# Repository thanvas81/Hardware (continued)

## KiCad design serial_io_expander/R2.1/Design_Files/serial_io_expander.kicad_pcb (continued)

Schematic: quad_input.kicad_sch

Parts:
D8, D13, D18, D23: TBAW56,LM; SOT-23
RN9: 120K; R_Array_Concave_4x0603
RN10: 47K; R_Array_Concave_4x0603
U5, U6: PUMH11,115; SOT-363_SC-70-6

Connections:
/digital_inputs/COLLECTOR1: U6.3; also elsewhere on the board
/digital_inputs/COLLECTOR2: U6.6; also elsewhere on the board
/digital_inputs/COLLECTOR3: U5.6; also elsewhere on the board
/digital_inputs/COLLECTOR4: U5.3; also elsewhere on the board
/digital_inputs/IN1: RN9.8 (R1.2), RN10.5 (R4.2); also elsewhere on the board
/digital_inputs/IN2: RN9.7 (R2.2), RN10.6 (R3.2); also elsewhere on the board
/digital_inputs/IN3: RN9.6 (R3.2), RN10.7 (R2.2); also elsewhere on the board
/digital_inputs/IN4: RN9.5 (R4.2), RN10.8 (R1.2); also elsewhere on the board
/digital_inputs/quad_input1/+PULLUP: D8.3 (A), D13.3 (A); also elsewhere on the board
GND: D18.3 (A), D23.3 (A), U5.1, U5.4, U6.1, U6.4; also elsewhere on the board
unnamed: D23.1 (K), RN9.1 (R1.1), U5.5
unnamed: D23.2 (K), RN9.2 (R2.1), U5.2
unnamed: D18.2 (K), RN9.3 (R3.1), U6.2
unnamed: D18.1 (K), RN9.4 (R4.1), U6.5
unnamed: D13.2 (K), RN10.1 (R1.1)
unnamed: D13.1 (K), RN10.2 (R2.1)
unnamed: D8.2 (K), RN10.3 (R3.1)
unnamed: D8.1 (K), RN10.4 (R4.1)

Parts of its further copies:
D3, D4, D6, D7, D9, D10, D11, D12, D14, D15, D16, D17, D19, D20, D21, D22: TBAW56,LM; SOT-23
RN11, RN13, RN15, RN17: 47K; R_Array_Concave_4x0603
RN12, RN14, RN16, RN18: 120K; R_Array_Concave_4x0603
U15, U16, U21, U22, U27, U28, U33, U34: PUMH11,115; SOT-363_SC-70-6

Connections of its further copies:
/digital_inputs/COLLECTOR5: U16.3; also elsewhere on the board
/digital_inputs/COLLECTOR6: U16.6; also elsewhere on the board
/digital_inputs/COLLECTOR7: U15.6; also elsewhere on the board
/digital_inputs/COLLECTOR8: U15.3; also elsewhere on the board
/digital_inputs/COLLECTOR9: U22.3; also elsewhere on the board
/digital_inputs/COLLECTOR10: U22.6; also elsewhere on the board
/digital_inputs/COLLECTOR11: U21.6; also elsewhere on the board
/digital_inputs/COLLECTOR12: U21.3; also elsewhere on the board
/digital_inputs/COLLECTOR13: U34.3; also elsewhere on the board
/digital_inputs/COLLECTOR14: U34.6; also elsewhere on the board
/digital_inputs/COLLECTOR15: U33.6; also elsewhere on the board
/digital_inputs/COLLECTOR16: U33.3; also elsewhere on the board
/digital_inputs/COLLECTOR17: U28.3; also elsewhere on the board
/digital_inputs/COLLECTOR18: U28.6; also elsewhere on the board
/digital_inputs/COLLECTOR19: U27.6; also elsewhere on the board
/digital_inputs/COLLECTOR20: U27.3; also elsewhere on the board
/digital_inputs/IN5: RN11.5 (R4.2), RN12.8 (R1.2); also elsewhere on the board
/digital_inputs/IN6: RN11.6 (R3.2), RN12.7 (R2.2); also elsewhere on the board
/digital_inputs/IN7: RN11.7 (R2.2), RN12.6 (R3.2); also elsewhere on the board
/digital_inputs/IN8: RN11.8 (R1.2), RN12.5 (R4.2); also elsewhere on the board
/digital_inputs/IN9: RN13.5 (R4.2), RN14.8 (R1.2); also elsewhere on the board
/digital_inputs/IN10: RN13.6 (R3.2), RN14.7 (R2.2); also elsewhere on the board
/digital_inputs/IN11: RN13.7 (R2.2), RN14.6 (R3.2); also elsewhere on the board
/digital_inputs/IN12: RN13.8 (R1.2), RN14.5 (R4.2); also elsewhere on the board
/digital_inputs/IN13: RN17.5 (R4.2), RN18.8 (R1.2); also elsewhere on the board
/digital_inputs/IN14: RN17.6 (R3.2), RN18.7 (R2.2); also elsewhere on the board
/digital_inputs/IN15: RN17.7 (R2.2), RN18.6 (R3.2); also elsewhere on the board
/digital_inputs/IN16: RN17.8 (R1.2), RN18.5 (R4.2); also elsewhere on the board
/digital_inputs/IN17: RN15.5 (R4.2), RN16.8 (R1.2); also elsewhere on the board
/digital_inputs/IN18: RN15.6 (R3.2), RN16.7 (R2.2); also elsewhere on the board
/digital_inputs/IN19: RN15.7 (R2.2), RN16.6 (R3.2); also elsewhere on the board
/digital_inputs/IN20: RN15.8 (R1.2), RN16.5 (R4.2); also elsewhere on the board
/digital_inputs/quad_input1/+PULLUP: D3.3 (A), D4.3 (A), D6.3 (A), D7.3 (A), D9.3 (A), D10.3 (A), D11.3 (A), D12.3 (A); also elsewhere on the board
GND: D14.3 (A), D15.3 (A), D16.3 (A), D17.3 (A), D19.3 (A), D20.3 (A), D21.3 (A), D22.3 (A), U15.1, U15.4, U16.1, U16.4, U21.1, U21.4, U22.1, U22.4, U27.1, U27.4, U28.1, U28.4, U33.1, U33.4, U34.1, U34.4; also elsewhere on the board
unnamed: D9.2 (K), RN11.1 (R1.1)
unnamed: D9.1 (K), RN11.2 (R2.1)
unnamed: D3.2 (K), RN11.3 (R3.1)
unnamed: D3.1 (K), RN11.4 (R4.1)
unnamed: D19.1 (K), RN12.1 (R1.1), U15.5
unnamed: D19.2 (K), RN12.2 (R2.1), U15.2
unnamed: D14.2 (K), RN12.3 (R3.1), U16.2
unnamed: D14.1 (K), RN12.4 (R4.1), U16.5
unnamed: D10.2 (K), RN13.1 (R1.1)
unnamed: D10.1 (K), RN13.2 (R2.1)
unnamed: D4.2 (K), RN13.3 (R3.1)
unnamed: D4.1 (K), RN13.4 (R4.1)
unnamed: D20.1 (K), RN14.1 (R1.1), U21.5
unnamed: D20.2 (K), RN14.2 (R2.1), U21.2
unnamed: D15.2 (K), RN14.3 (R3.1), U22.2
unnamed: D15.1 (K), RN14.4 (R4.1), U22.5
unnamed: D11.2 (K), RN15.1 (R1.1)
unnamed: D11.1 (K), RN15.2 (R2.1)
unnamed: D6.2 (K), RN15.3 (R3.1)
unnamed: D6.1 (K), RN15.4 (R4.1)
unnamed: D21.1 (K), RN16.1 (R1.1), U27.5
unnamed: D21.2 (K), RN16.2 (R2.1), U27.2
unnamed: D16.2 (K), RN16.3 (R3.1), U28.2
unnamed: D16.1 (K), RN16.4 (R4.1), U28.5
unnamed: D12.2 (K), RN17.1 (R1.1)
unnamed: D12.1 (K), RN17.2 (R2.1)
unnamed: D7.2 (K), RN17.3 (R3.1)
unnamed: D7.1 (K), RN17.4 (R4.1)
unnamed: D22.1 (K), RN18.1 (R1.1), U33.5
unnamed: D22.2 (K), RN18.2 (R2.1), U33.2
unnamed: D17.2 (K), RN18.3 (R3.1), U34.2
unnamed: D17.1 (K), RN18.4 (R4.1), U34.5

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
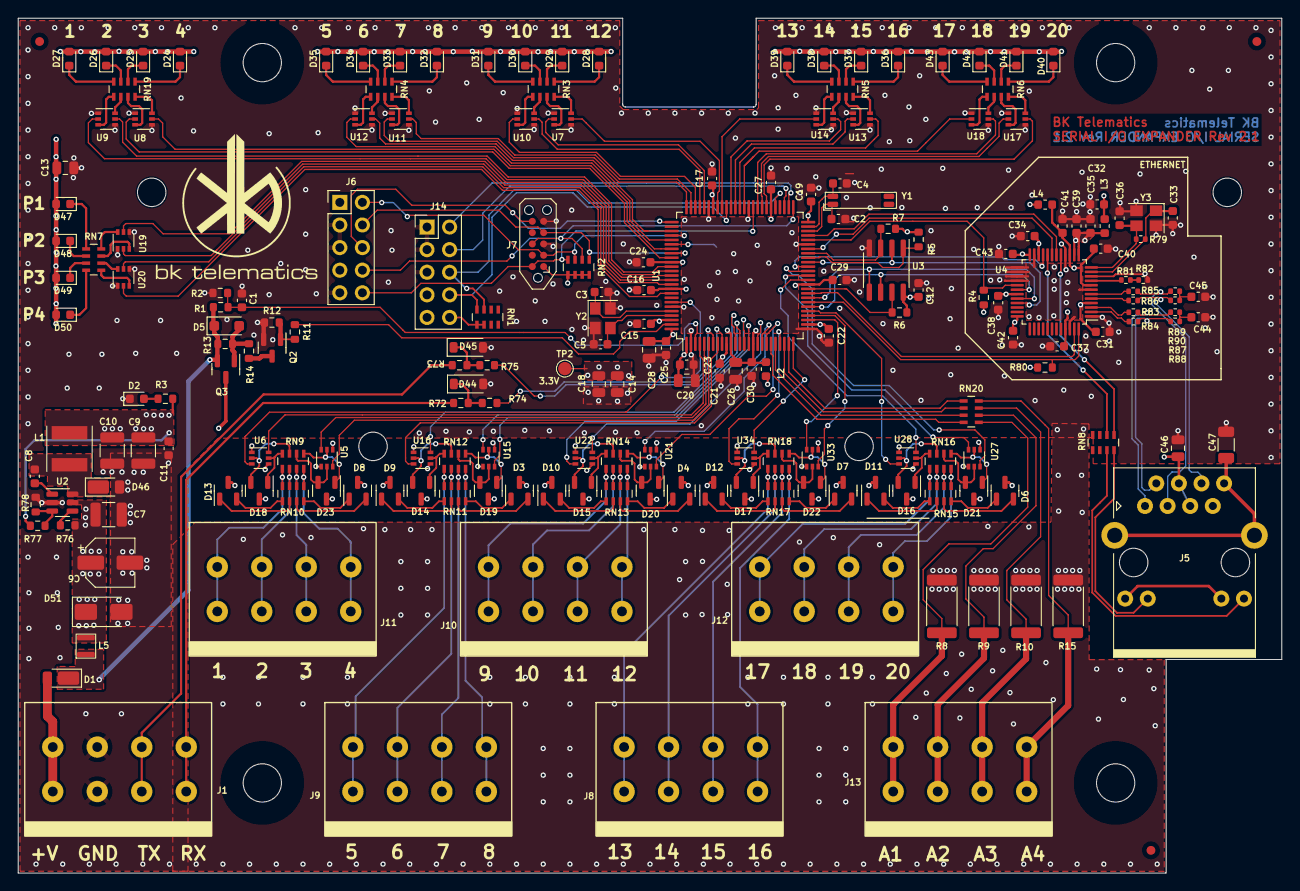
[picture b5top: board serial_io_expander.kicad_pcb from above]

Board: 4 copper layers, 142.0 x 96.1 mm, 212 parts (1 on the bottom side), 232 nets.

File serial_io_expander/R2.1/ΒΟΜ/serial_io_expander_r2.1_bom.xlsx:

Reference | Qty | Value | Manufacturer | Part No | Description | Footprint | DNP
C1, C8, C11, C12, C15, C16, C17, C19, C21, C22, C23, C24, C25, C27, C29, C30, C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 | 28 | 0.1u | Wurth Elektronik | 885012206095 | MLCC SMD 0.1uF 0603 10% 50V | 0603
C2, C3, C4, C5 | 4 | 18pF | Walsin | 0603N180J160CT | MLCC 50 V 18 pF C0G 0603 5% | 0603
C6 | 1 | 10u | Wurth Elektronik | 865080642006 | Aluminium Electrolytic Capacitors - SMD 50V 10uF 5X5.3 | CP_Elec_5x5.3
C7 | 1 | 2.2u | Samsung Electro-Mechanics | CL32B225KBJNNNE | MLCC SMD 2.2uF 10% 50V X7R 1210 | 1210
C9, C10 | 2 | 22u | Samsung Electro-Mechanics | CL32A226MOJNNNE | MLCC - SMD/SMT 22uF+/-10% 10V X5R 3 1210 | 1210
C13, C18 | 2 | 10u | Samsung Electro-Mechanics | CL21A106KOQNNNF | MLCC - SMD 10uF 10% 16V X5R 2 0805 | 0805
C14, C20, C26, C28 | 4 | 4.7u | Samsung Electro-Mechanics | CL21A475KAQNNNE | MLCC - SMD 4.7uF 10% 16V X5R 0805 | 0805
C33, C36 | 2 | 12p | Samsung Electro-Mechanics | CL10C120JB81PNC | MLCC - SMD 12pF 5%, 50V | 0603
C39 | 1 | 3.3u | TDK | C1608X6S1C335K080AC | MLCC - SMD 3.3uF 10% 10V X5R 0603 | 0603
C46 | 1 | 1u | Walsin | 0805B105K160CT | MLCC - SMD 50V 1uF X7R 0805 10% | 0805
C47 | 1 | 1n/2kV | Wurth Elektronik | 885342208024 | MLCC - SMD/SMT 2Kvolts 1000pF 10% X7R | 1206
D1, D46 | 2 | SBR3U60P1Q-7 | Diodes Incorporated | SBR3U60P1Q-7 | Schottky Diodes & Rectifiers 3A SBR 60Vrrm 3A 0.62Vf 100Ir | PowerDI-123-2
D2, D24, D25, D26, D27, D28, D29, D30, D31, D32, D33, D34, D35, D36, D37, D38, 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 | 25 | LED_Small_Filled | Kingbright | APT1608SEC/J3-AMT | Standard LEDs - SMD 1.6x0.8mm Red | 0603
D3, D4, D6, D7, D8, D9, D10, D11, D12, D13, D14, D15, D16, D17, D18, D19, D20, 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 | 20 | TBAW56,LM | Toshiba | TBAW56,LM | Schottky Diodes & Rectifiers Switching Diode 80V 215mA | SOT-23
D5 | 1 | 8.2V | Panjit | BZT52-B8V2_R1_00001 | Zener Diodes 8.2 Volt 0.5W 2% | SOD-123F
D44, D45 | 2 | 3V | Micro Commercial Components (MCC) | MMSZ4684-TP | Zener Diodes 3.3V 500mW 7.5uA | SOD-123
D51 | 1 | SMAJ40CAe3/TR13 | Microchip Technology | SMAJ40CAe3/TR13 | ESD Suppressors / TVS Diodes TVS | SMA
J1, J8, J9, J10, J11, J12, J13 | 7 | Conn_01x04 | MULTICOMP | MP008126 | Wire-To-Board Terminal Block, 5 mm, 4 Ways, 28 AWG, 12 AWG, Clamp | -
J5 | 1 | ARJM11B1-009-AB-EW2 | ABRACON | ARJM11B1-009-AB-EW2 | Ethernet Connector RJ45 JACK W/MAG 1X1 100BASE-T | -
J6 | 1 | - | - | - | Header pin 2x5 2.54mm vertical | - | 1
J14 | 1 | - | - | - | Header pin 2x5 2.54mm vertical | - | 1
L1 | 1 | 22uH | TAIYO YUDEN | NRS5020T220MMGJ | Power inductor 22uH 20% 1A | 5020
L2 | 1 | 10uH | TDK | MLZ1608E100MT | Power Inductors - SMD 0603 10uH 20% | 0603
L3, L4 | 2 | Ferrite 300 Ohm | Coiltronics / Eaton | MFBA2V1608-301-R | Ferrite Beads Ferrite B IND 300 OHM 1A 2 PADS SMT | 0603
L5 | 1 | 4.7uH | TDK | VLS252012HBX-4R7M-1 | Power Inductors SMD 4.7uH 1.9A 240mOhms Power Circuits | 1008
Q2 | 1 | MMBT3904 | Taiwan Semiconductor | MMBT3904 RFG | Bipolar Transistors - BJT 60V, 0.2A, NPN Bipolar Transistor | SOT-23
Q3 | 1 | BSS84 | Nexperia | BSS84AK,215 | P channel mosfet SMD 180mA 1 channel 50V SOT-23 | SOT-23
R1, R4, R5, R6, R7, R76 | 6 | 100K | Vishay / Dale | CRCW0603100KFKEA | CHIP RES 100K 0603 1% SMD | 0603
R2, R11, R12, R13, R14, R78, R80 | 7 | 10K | Panasonic | ERJ-3EKF1002V | CHIP RES 10K 0603 1% SMD | 0603
R3 | 1 | 470R | YAGEO | AC0603JR-7W470RL | CHIP RES 470Ω 0603 5% SMD | 0603
R8, R9, R10, R15 | 4 | 150R | TE Connectivity / Holsworthy | CRGP2512F150R | CHIP RES 150Ω 2512 1% SMD 2W | 2512
R72, R73 | 2 | 4K7 | YAGEO | RT0603FRE074K7L | CHIP RES 4.7K 1% 0603 SMD | 0603
R74, R75 | 2 | 100R | YAGEO | RT0603FRE10100RL | CHIP RES 100Ω 0603 1% SMD | 0603
R77 | 1 | 33K | YAGEO | RT0603FRE1033KL | CHIP RES 33K 1% 0603 SMD | 0603
R79 | 1 | 1M | - | - | - | 0402 | 1
R81 | 1 | 300R | YAGEO | RT0402FRE07300RL | CHIP RES 300Ω 1% 0402 SMD | 0402
R82 | 1 | 12K | Bourns | CR0402-FX-1202GLF | CHIP RES 12K 1% 0402 SMD | 0402
R83, R84, R85, R86 | 4 | 3R3 | Bourns | CR0402-F/-3R30GLF | CHIP RES 3.3Ω 1% 0402 SMD | 0402
R87, R88, R89, R90 | 4 | 49R9 | YAGEO | RT0402FRE0749R9L | CHIP RES 49.9Ω 1% 0402 SMD | 0402
RN1 | 1 | 4K7 | IRC | BCN164A472J13 | RES NET 4.7K 5% 1206 SMD | 1206
RN2 | 1 | 100K | Bourns | CAY16-1003F4LF | RES NET 100K 1% 1206 SMD | 1206
RN3, RN4, RN5, RN6, RN7, RN19 | 6 | R_Pack04_Split | Bourns | CAT16-1800F4LF | RES NET 180Ω 1% 1206 SMD | 1206
RN8 | 1 | 470R | Bourns | CAT16-4700F4LF | RES NET 470Ω 1% 1206 SMD | 1206
RN9, RN12, RN14, RN16, RN18 | 5 | 120K | Bourns | CAT16-124J4LF | RES NET 120K 1% 1206 SMD | 1206
RN10, RN11, RN13, RN15, RN17 | 5 | 47K | Bourns | CAT16-4702F4LF | RES NET 47K 1% 1206 SMD | 1206
RN20 | 1 | 10K | Bourns | CAT16-103J4LF | RES NET 10K 5% 1206 SMD | 1206
U1 | 1 | ATSAM4S4C | Microchip Technology | ATSAM4S4CA-AUR | ARM MCU ATSAM4S4C Microchip 100LQFP | LQFP100
U2 | 1 | LV2862x | Texas Instruments | LV2862XLVDDCR | Switching Voltage Regulators 4.5-V to 60-V, 600-mA buck converter in ultra-smal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 | SOT-23-6
U3 | 1 | AT25SF321B-SSHB-X | Renesas / Dialog | AT25SF321B-SSHB-T | NOR Flash 32 Mbit, 3.0V (2.7V to 3.6V), -40C to 85C, SOIC-N 150mil (Tape & Reel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 | SOIC8
U4 | 1 | W6100L | WIZnet | W6100L | Ethernet ICs 3-in-1 Ethernet Controller : TCP/IP +MAC+PHY | LQFP48
U5, U6, U7, U8, U9, U10, U11, U12, U13, U14, U15, U16, U17, U18, U19, U20, U21,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 | 22 | PUMH11,115 | Nexperia | PUMH1,115 | Bipolar Transistors - Pre-Biased PUMH1/SOT363/SC-88 | SOT-363
Y1 | 1 | 9HT7-32.768KDZF-T | TXC Corporation | WC146SMF-32.768KHZ-T | Crystals 32.768KHz 20ppm 12.5pF | -
Y2 | 1 | 12MHz | ABRACON | ABM8G-12.000MHZ-18-D2Y-T | Crystals AEC-Q200 12MHz 8pF 3.2x2.5mm | -
Y3 | 1 | 25MHz | ABRACON | ABM8G-25.000MHZ-18-D2Y-T | Crystal 25MHz SMD | -

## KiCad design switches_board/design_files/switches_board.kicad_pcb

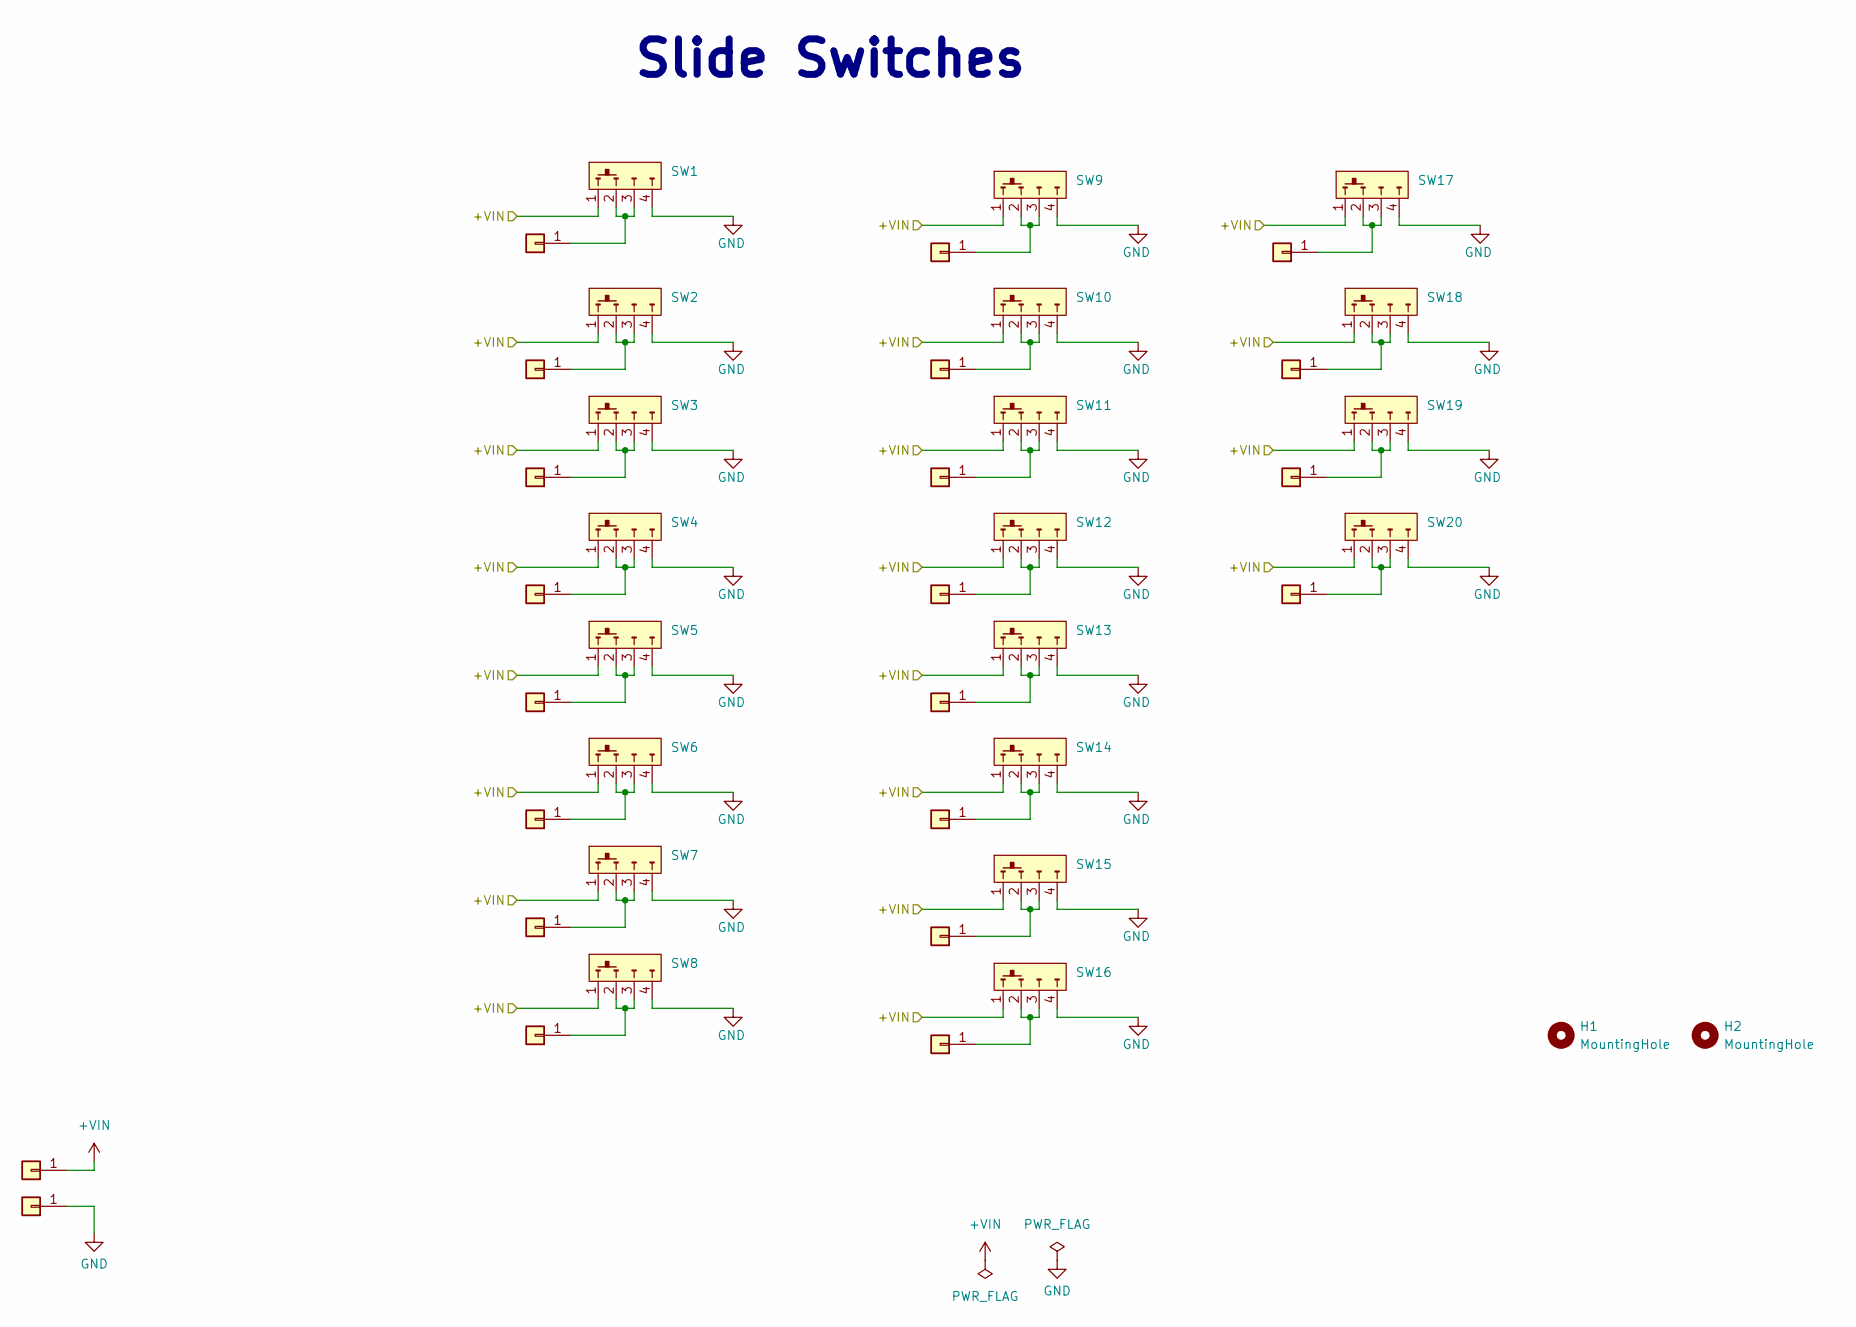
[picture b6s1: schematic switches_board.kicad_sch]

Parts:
H1, H2: MountingHole; MountingHole_3.2mm_M3_DIN965
J1, J2, J3, J4, J5, J6, J7, J8, J9, J10, J11, J12, J13, J14, J15, J16, J17, J18, J19, J20, J21, J22: Conn_01x01; Simple_hole_pad_3x1.5
SW1, SW2, SW3, SW4, SW5, SW6, SW7, SW8, SW9, SW10, SW11, SW12, SW13, SW14, SW15, SW16, SW17, SW18, SW19, SW20: SLW-156646-5A-N-D; PartID 999

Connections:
+VIN: J1.1, SW1.1, SW2.1, SW3.1, SW4.1, SW5.1, SW6.1, SW7.1, SW8.1, SW9.1, SW10.1, SW11.1, SW12.1, SW13.1, SW14.1, SW15.1, SW16.1, SW17.1, SW18.1, SW19.1, SW20.1
GND: J2.1, SW1.4, SW2.4, SW3.4, SW4.4, SW5.4, SW6.4, SW7.4, SW8.4, SW9.4, SW10.4, SW11.4, SW12.4, SW13.4, SW14.4, SW15.4, SW16.4, SW17.4, SW18.4, SW19.4, SW20.4
unnamed: J3.1, SW1.2, SW1.3
unnamed: J4.1, SW2.2, SW2.3
unnamed: J5.1, SW3.2, SW3.3
unnamed: J6.1, SW4.2, SW4.3
unnamed: J7.1, SW5.2, SW5.3
unnamed: J8.1, SW6.2, SW6.3
unnamed: J9.1, SW7.2, SW7.3
unnamed: J10.1, SW8.2, SW8.3
unnamed: J11.1, SW9.2, SW9.3
unnamed: J12.1, SW10.2, SW10.3
unnamed: J13.1, SW11.2, SW11.3
unnamed: J14.1, SW12.2, SW12.3
unnamed: J15.1, SW13.2, SW13.3
unnamed: J16.1, SW14.2, SW14.3
unnamed: J17.1, SW15.2, SW15.3
unnamed: J18.1, SW16.2, SW16.3
unnamed: J19.1, SW17.2, SW17.3
unnamed: J20.1, SW18.2, SW18.3
unnamed: J21.1, SW19.2, SW19.3
unnamed: J22.1, SW20.2, SW20.3

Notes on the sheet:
Slide Switches

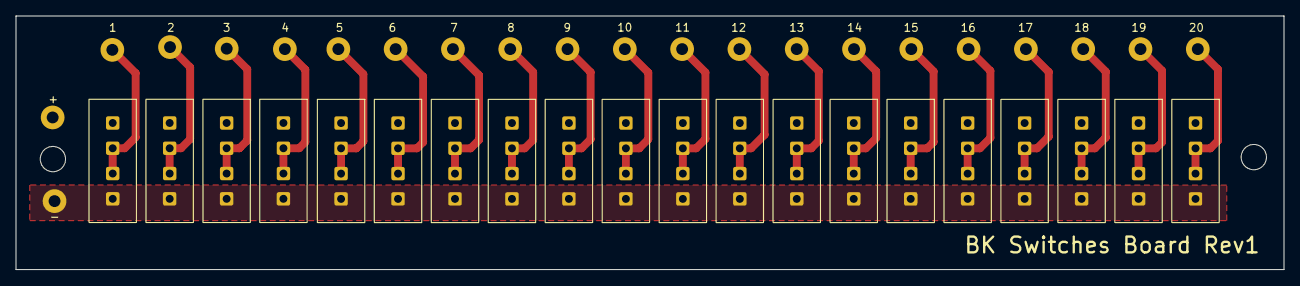
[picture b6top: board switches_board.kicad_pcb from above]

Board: 2 copper layers, 160.5 x 32.1 mm, 44 parts (0 on the bottom side), 22 nets.
